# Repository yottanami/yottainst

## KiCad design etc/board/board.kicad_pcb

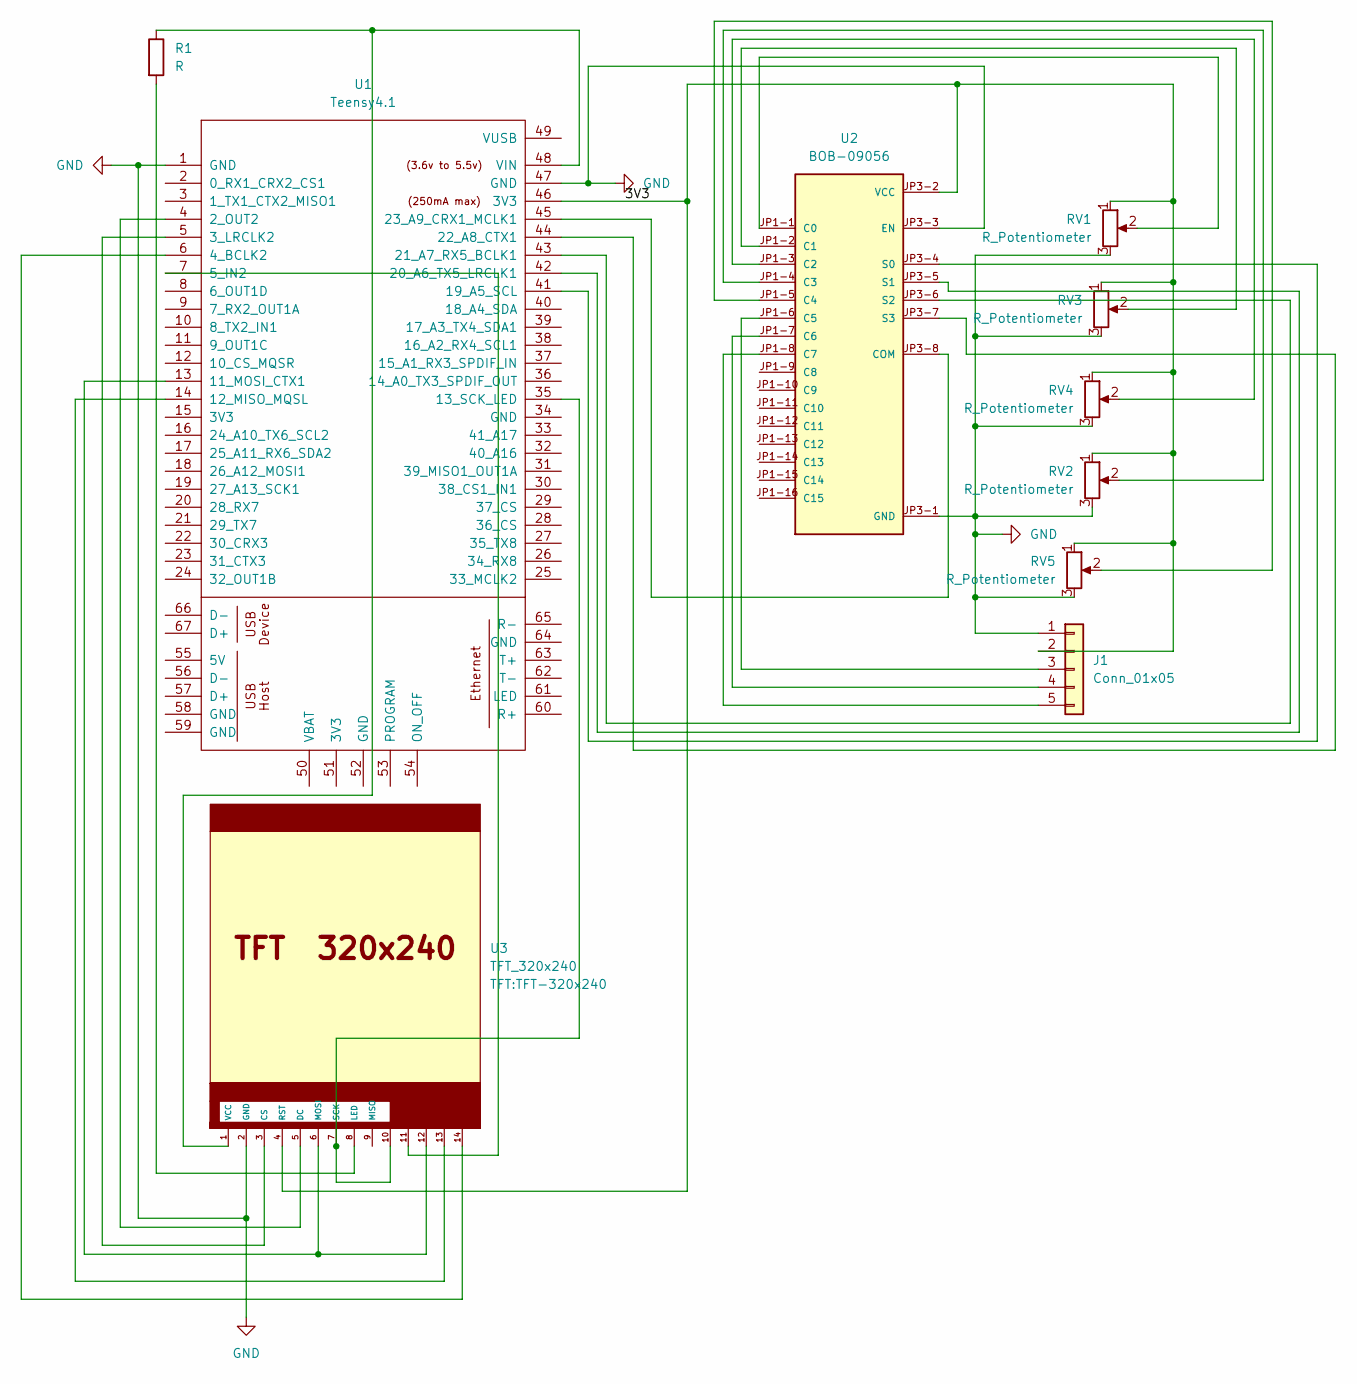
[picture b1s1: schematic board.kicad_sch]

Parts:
J1: Conn_01x05; PinHeader_1x05_P2.54mm_Vertical
R1: R; R_Axial_DIN0204_L3.6mm_D1.6mm_P1.90mm_Vertical
RV1, RV2, RV3, RV4, RV5: R_Potentiometer; Potentiometer_Omeg_PC16BU_Vertical
U1: Teensy4.1; Teensy
U2: BOB-09056; MODULE_BOB-09056; PARTREV v11
U3: TFT_320x240; TFT-320x240

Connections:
/3V3: J1.2, RV1.1, RV2.1, RV3.1, RV4.1, RV5.1, U1.46 (3V3), U2.JP3-2 (VCC), U3.4 (RST)
GND: J1.1, RV1.3, RV2.3, RV3.3, RV4.3, RV5.3, U1.1 (GND), U1.47 (GND), U2.JP3-1 (GND), U2.JP3-3 (EN), U3.2 (GND)
unnamed: J1.3, U2.JP1-6 (C5)
unnamed: J1.4, U2.JP1-7 (C6)
unnamed: J1.5, U2.JP1-8 (C7)
unnamed: U1.4 (2_OUT2), U3.5 (DC)
unnamed: U1.5 (3_LRCLK2), U3.3 (CS)
unnamed: U1.6 (4_BCLK2), U3.14
unnamed: U1.7 (5_IN2), U3.11
unnamed: U1.13 (11_MOSI_CTX1), U3.6 (MOSI), U3.12
unnamed: U1.14 (12_MISO_MQSL), U3.13
unnamed: U1.35 (13_SCK_LED), U3.7 (SCK), U3.10
unnamed: U1.41 (19_A5_SCL), U2.JP3-4 (S0)
unnamed: U1.42 (20_A6_TX5_LRCLK1), U2.JP3-5 (S1)
unnamed: U1.43 (21_A7_RX5_BCLK1), U2.JP3-6 (S2)
unnamed: U1.44 (22_A8_CTX1), U2.JP3-7 (S3)
unnamed: U1.45 (23_A9_CRX1_MCLK1), U2.JP3-8 (COM)
unnamed: R1.1, U1.48 (VIN), U3.1 (VCC)
unnamed: RV1.2, U2.JP1-1 (C0)
unnamed: RV3.2, U2.JP1-2 (C1)
unnamed: RV4.2, U2.JP1-3 (C2)
unnamed: RV2.2, U2.JP1-4 (C3)
unnamed: RV5.2, U2.JP1-5 (C4)
unnamed: R1.2, U3.8 (LED)

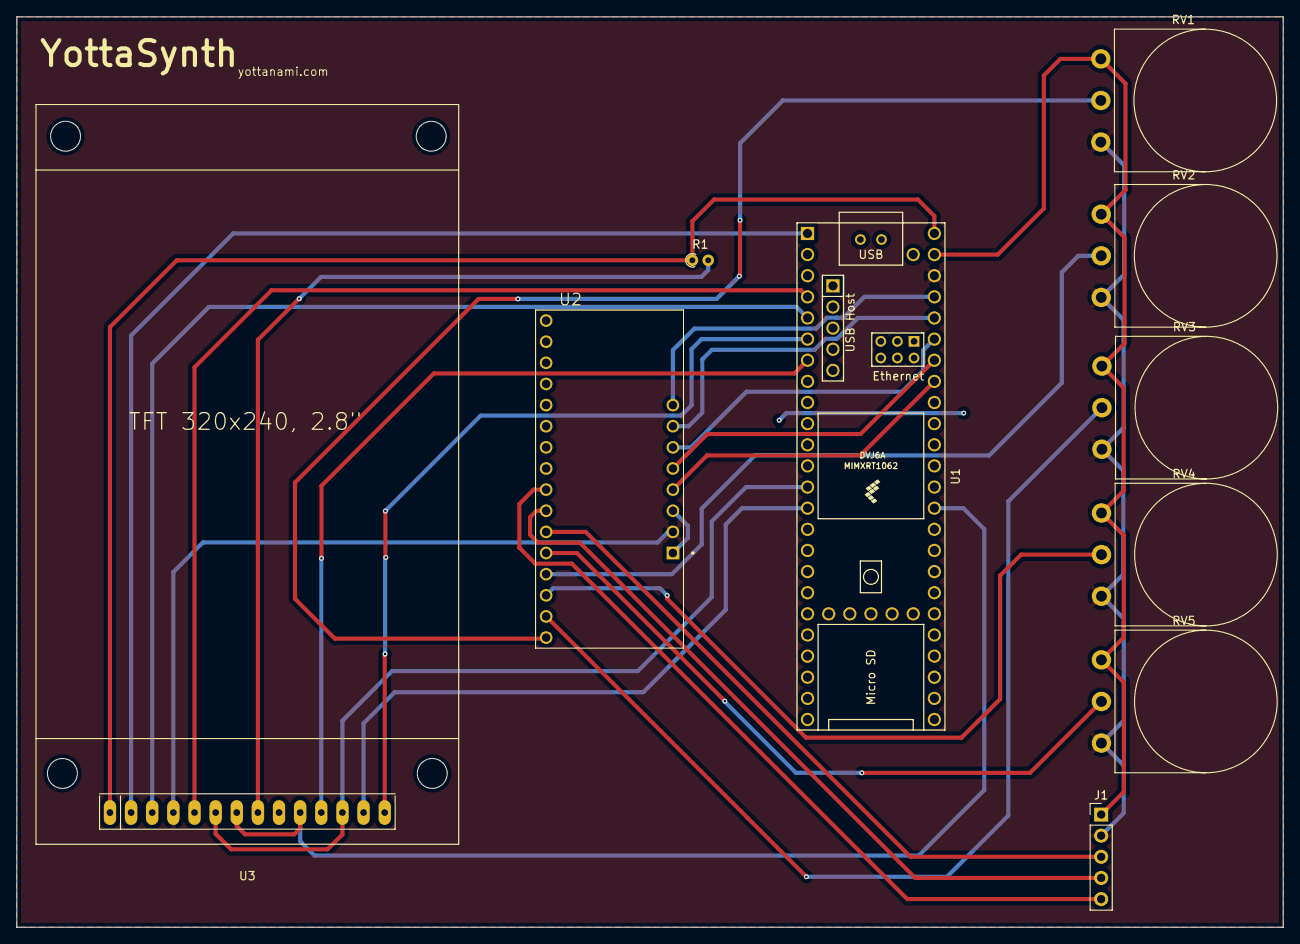
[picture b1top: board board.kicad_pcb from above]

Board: 2 copper layers, 152.2 x 109.4 mm, 10 parts (0 on the bottom side), 24 nets.

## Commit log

2024-03-04 Add main menu and fix touch issues
2024-03-04 Add settings and test synth output
2024-03-05 Upate synth to use puredata
2024-03-07 Add MIDI read to synth
2024-03-07 Add envelope
2024-03-07 Add filter
2024-03-08 Fix filter issues
2024-03-08 Add bend
2024-03-08 Add LFO
2024-03-14 Create Synth class
2024-03-17 Improve synth class and add play mode
2024-04-11 Latest changes
2025-09-18 Set teensy-cli as upload protocol of Platformio
2025-09-18 Introduce Settings
2025-09-18 Create main menu
2025-09-18 Add board files
2025-09-18 Add USB_MIDI flag and clean up the main file
2025-09-19 Update gitignore
2025-11-19 Make a working version with simple loop
2025-11-20 MIDI and audio both works
2025-11-20 Restore envelope pin comments
